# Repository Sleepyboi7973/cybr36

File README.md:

# cybr36
 The cybr36 is a no frills, wireless, 36 key, column-staggered keyboard sporting button cell batteries and nice!nano controllers.

<br>

<br>

<br>

<br>

<br>

<br>

## Firmware
The cybr36 runs ZMK firmware which can be found on my profile [here](https://github.com/Sleepyboi7973/zmk-config-cybr36).

## Case Printing Tips
Print the plate at 100% size and the case at 101.5% size to ensure that the pcb and plate fit inside without issue. I printed my case with no top or bottom layers, no supports, and triangular infill at 30%

## Build Guide

### Bill of Materials:
| BOM                          |    |
|------------------------------|----|
| PCB                          | 2  |
| Plate                        | 2  |
| Case                         | 2  |
| Rubber Feet                  | 10 |
| 10mm M2 Screw                | 8  |
| nice!nano V2                 | 2  |
| 1x12 Pin Header              | 4  |
| MX Switches                  | 36 |
| MX 1u Keycaps                | 36 |
| MX Hotswap Sockets           | 36 |
| SOD-123 1N4148 Diodes        | 36 |
| PCM12/MSK12 SMD Slide Switch | 2  |
| 3x4x2mm 2 Pin SMD Button     | 2  |
| 2430 Battery Holder          | 2  |
| 2430 Battery                 | 2  |

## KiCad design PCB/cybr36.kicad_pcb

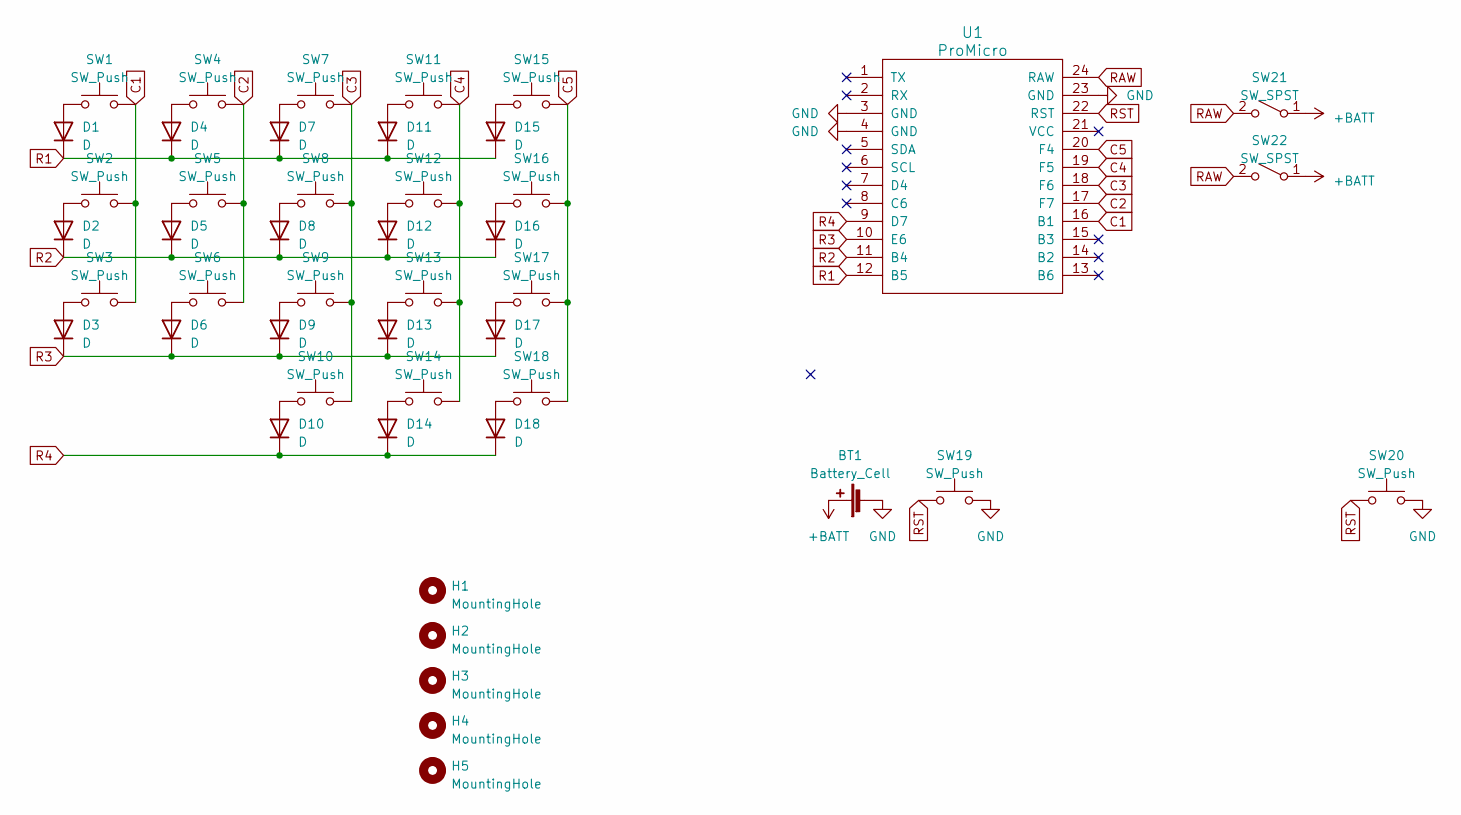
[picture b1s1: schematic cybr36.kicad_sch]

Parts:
BT1: Battery_Cell; 2430Holder
D1, D2, D3, D4, D5, D6, D7, D8, D9, D10, D11, D12, D13, D14, D15, D16, D17, D18: D; SOD123_DUALSIDE
H1, H2, H3, H4, H5: MountingHole; MountingHole_3.2mm_M3
SW1, SW2, SW3, SW4, SW5, SW6, SW7, SW8, SW9, SW10, SW11, SW12, SW13, SW14, SW15, SW16, SW17, SW18: SW_Push; MXReversible
SW19, SW20: SW_Push; RSTbutton
SW21, SW22: SW_SPST; SW_SPDT_PCM12
U1: ProMicro; ProMicro_v2

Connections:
+BATT: BT1.1 (+), SW21.1 (A), SW22.1 (A)
C1: SW1.2, SW2.2, SW3.2, U1.16 (B1)
C2: SW4.2, SW5.2, SW6.2, U1.17 (F7)
C3: SW7.2, SW8.2, SW9.2, SW10.2, U1.18 (F6)
C4: SW11.2, SW12.2, SW13.2, SW14.2, U1.19 (F5)
C5: SW15.2, SW16.2, SW17.2, SW18.2, U1.20 (F4)
GND: BT1.2 (-), SW19.2, SW20.2, U1.3 (GND), U1.4 (GND), U1.23 (GND)
unnamed: D1.2 (A), SW1.1
unnamed: D2.2 (A), SW2.1
unnamed: D3.2 (A), SW3.1
unnamed: D4.2 (A), SW4.1
unnamed: D5.2 (A), SW5.1
unnamed: D6.2 (A), SW6.1
unnamed: D7.2 (A), SW7.1
unnamed: D8.2 (A), SW8.1
unnamed: D9.2 (A), SW9.1
unnamed: D10.2 (A), SW10.1
unnamed: D11.2 (A), SW11.1
unnamed: D12.2 (A), SW12.1
unnamed: D13.2 (A), SW13.1
unnamed: D14.2 (A), SW14.1
unnamed: D15.2 (A), SW15.1
unnamed: D16.2 (A), SW16.1
unnamed: D17.2 (A), SW17.1
unnamed: D18.2 (A), SW18.1
R1: D1.1 (K), D4.1 (K), D7.1 (K), D11.1 (K), D15.1 (K), U1.12 (B5)
R2: D2.1 (K), D5.1 (K), D8.1 (K), D12.1 (K), D16.1 (K), U1.11 (B4)
R3: D3.1 (K), D6.1 (K), D9.1 (K), D13.1 (K), D17.1 (K), U1.10 (E6)
R4: D10.1 (K), D14.1 (K), D18.1 (K), U1.9 (D7)
RAW: SW21.2 (B), SW22.2 (B), U1.24 (RAW)
RST: SW19.1, SW20.1, U1.22 (RST)

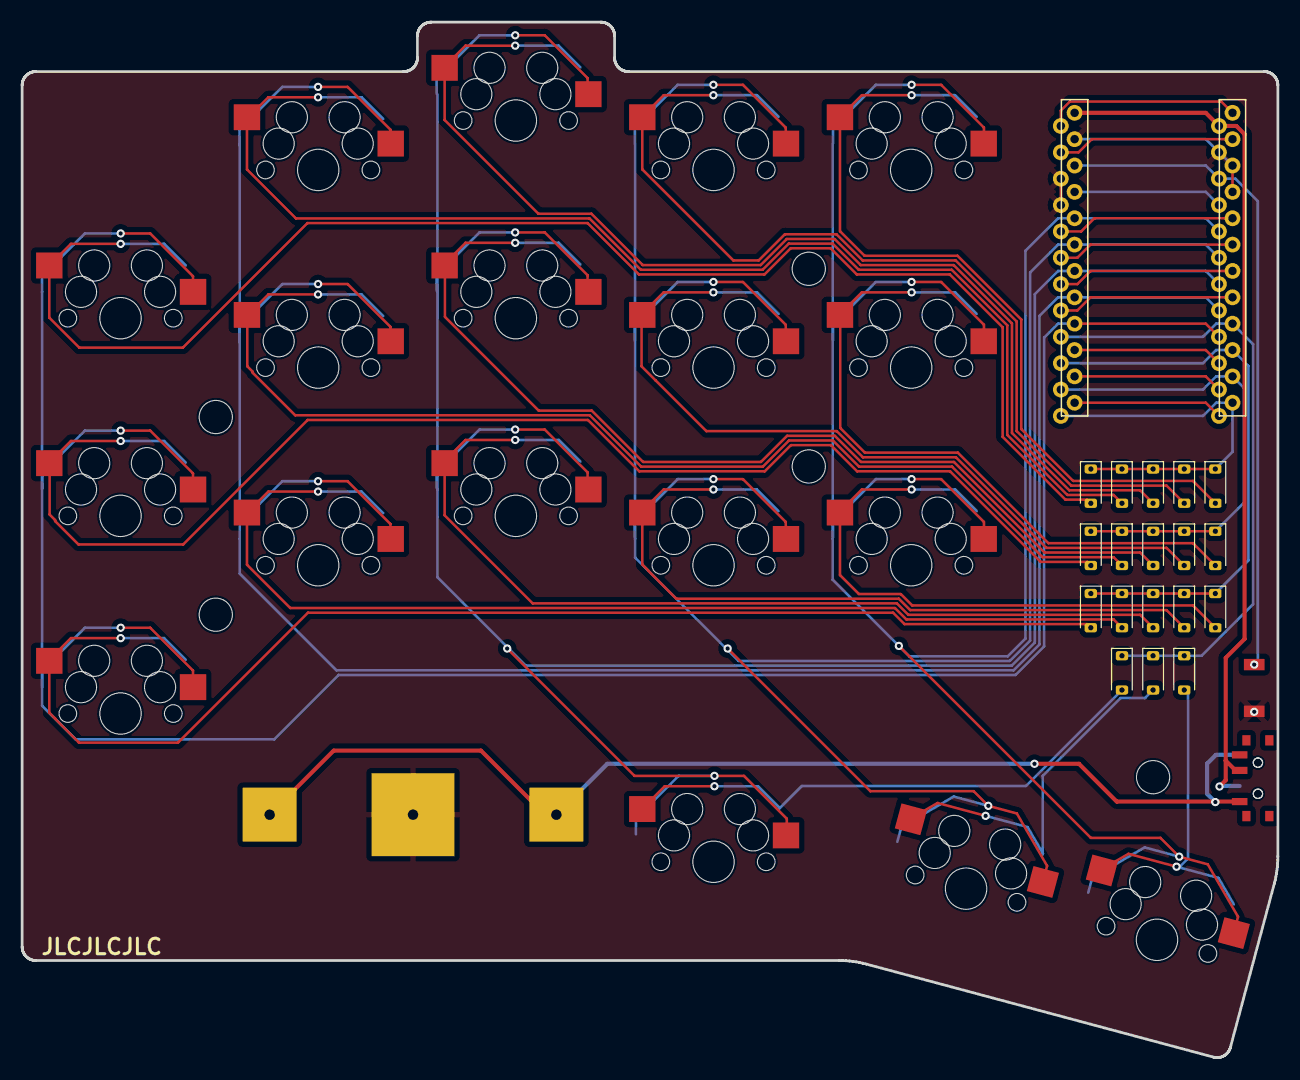
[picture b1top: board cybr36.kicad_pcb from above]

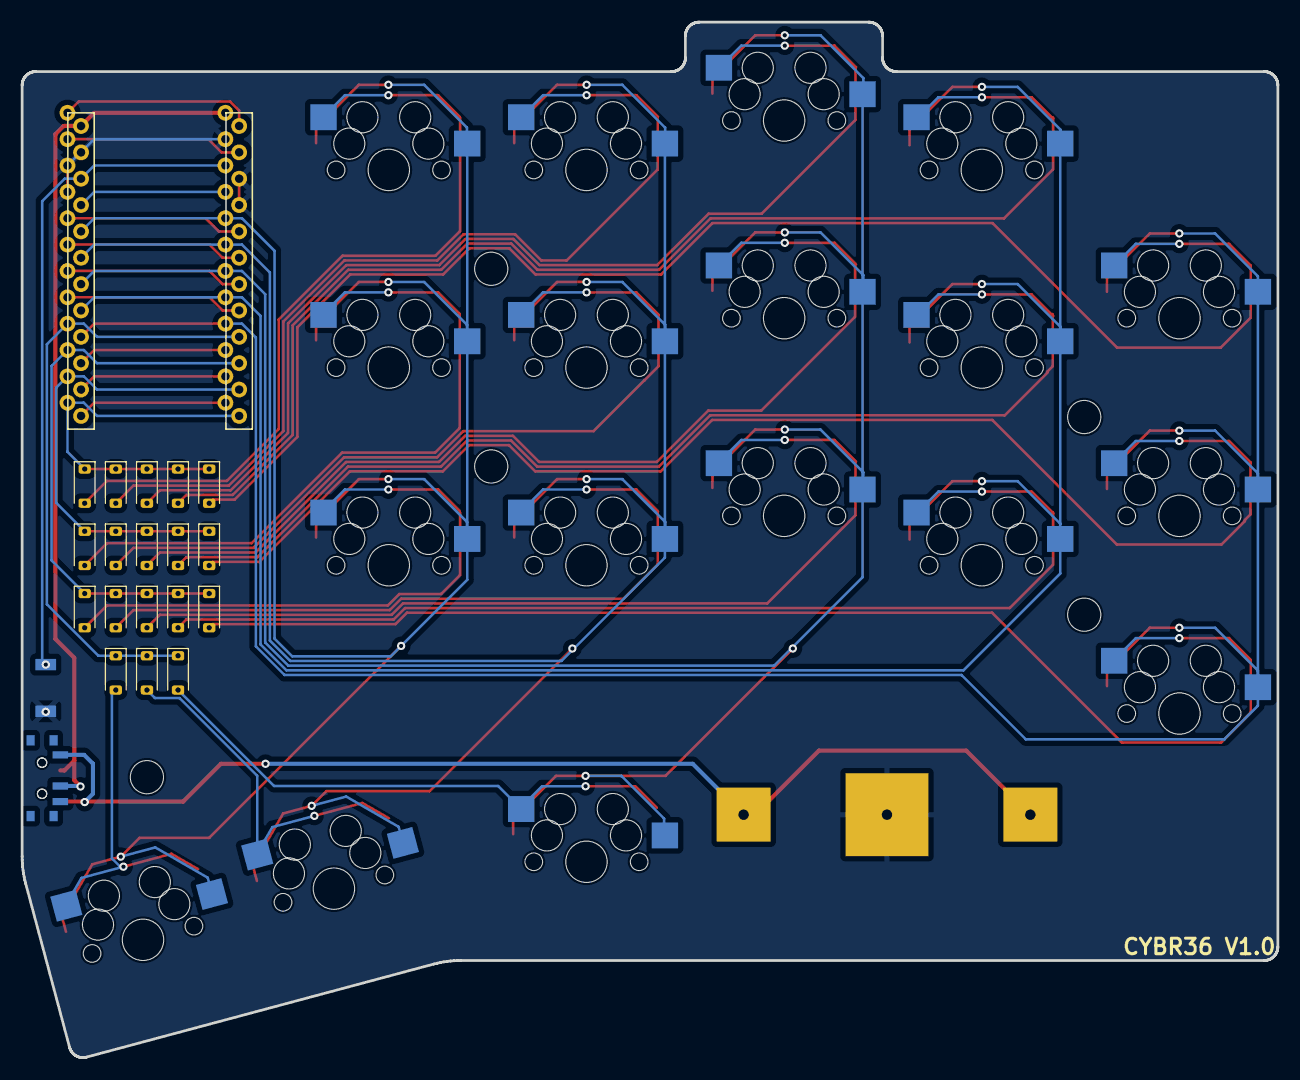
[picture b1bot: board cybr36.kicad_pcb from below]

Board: 2 copper layers, 121.0 x 99.8 mm, 47 parts (2 on the bottom side), 31 nets.

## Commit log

2023-11-15 case added
2023-11-18 power switch added
2023-11-18 no gerber lmao
2023-11-18 images and things
2023-11-18 more
